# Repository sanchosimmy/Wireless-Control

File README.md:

/**
@mainpage Wireless home appliances control.

@author Akshay Pampatwar (Software)
@author Sancho Simmy Louis (Hardware Circuit Design)
@author Nijil George (Android App)
@author Sabitha Susan Joseph (PCB Design)

Appliances can be controlled via switches on a control board or a bluetooth mobile app. This project is developed for Tiva C tm4c123gh6pm uC. It can control following appliances:

(i)Fan

(ii)12 V Led strip

(iii)Plug1

(iv)Plug2

Hardware profiling of fan is done in the code thus even in case of low or over voltage of AC main line, Fan speed will remain constant for a given setting.
User specific setting of fan speed,led light brightness can be enabled from bluetooth app. 

In the starting, stored i.e. last values of Fan speed and Led Intensity will be used for control. 
Remainig inputs will be taken from hardware control panel i.e. switch board.
Thus in case of electricity failure, Fan speed and Led light brighteness will be restored but on/off state of appliances will depend on states of switches. User will have to resend commands via app for wireless control.

In case of multiple users, Latest command will be considered. 
Once commands are sent over a bluetooth, o/p states will remain unnchanged even if wireless link is lost. i.e. Switch status will be ignored, But changes in switch will be incorporarted. 
E.g. Currently switch for fan is on and fan is on. Now if turn off command sent wirelessly then fan will turned off. But if switch for fan is toggled from on to off and off to on then fan will be turned on (Even if wireless link exists thus latest command is considered for final state of o/p).

	Software is divided into 3 layers.

(i)Application layer

(ii)Middle layer

(iii)Hardware Abstraction layer

For time being, for simplicity many HAL functions are defined in a Middle layer files/module. e.g. Bluetooth,fan,led,plug etc.

	Working of code: 

(i) First code initializes all the o/p pins and i/p pins. Initiallly all the o/ps are off.

(ii)Status of fan speed and led light intensity is restored from eeprom.

(iii)Depending on status of switches appliances will be turned on.

(iv)If data is sent over a bluetooth then it will be decoded and stored in a global variable.

(v)Controller continuously checks changes in states of appliances (From Switchs or Wi Command) Depending on new commands will be enforced for turning on/off or change of speed of appliances.

(vi)New commands of fan speed and intensity will be saved in an eeprom.

	Read files from Documentation\html folder for more info on software / code.
*/

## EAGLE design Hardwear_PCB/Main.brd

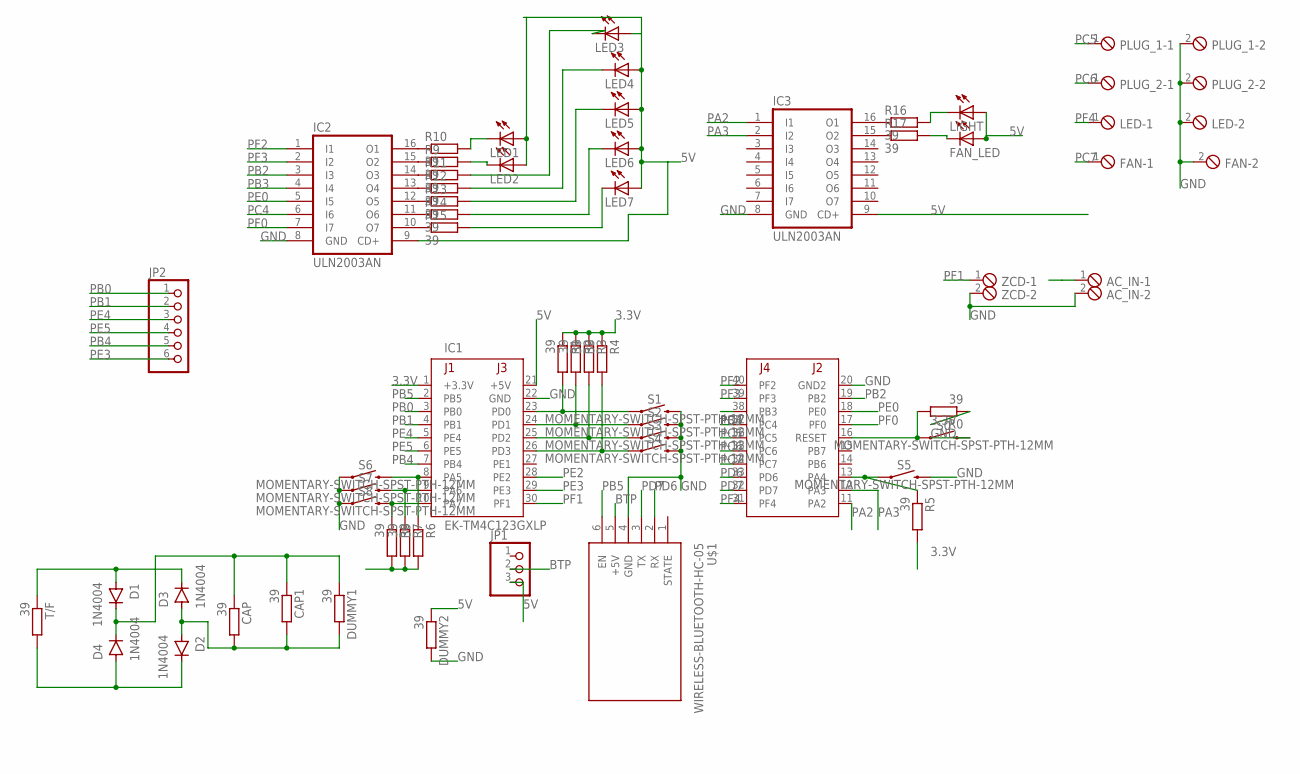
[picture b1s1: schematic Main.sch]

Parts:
AC_IN: MPT2; 2POL254
CAP, CAP1: 39; 0204/7
D1, D2, D3, D4: 1N4004; DO-41
DUMMY1, DUMMY2: 39; 0204/7
FAN: MPT2; 2POL254
FAN_LED: LED3MM
IC1: EK-TM4C123GXLP; TM4C123LAUNCHPAD
IC2, IC3: ULN2003AN; DIL16
JP1: PINHD-1X3CB; 1X03-CLEANBIG
JP2: PINHD-1X6; 1X06
LED: MPT2; 2POL254
LED1, LED2, LED3, LED4, LED5, LED6, LED7: LED3MM
LIGHT: LED3MM
PLUG_1, PLUG_2: MPT2; 2POL254
R0, R1, R2, R3, R4, R5, R6, R7, R8, R9, R10, R11, R12, R13, R14, R15, R16, R17: 39; 0204/7
S0, S1, S2, S3, S4, S5, S6, S7, S8: MOMENTARY-SWITCH-SPST-PTH-12MM; TACTILE_SWITCH_PTH_12MM
T/F: 39; 0204/7
U$1: WIRELESS-BLUETOOTH-HC-05
ZCD: MPT2; 2POL254

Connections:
3.3V: IC1.1 (+3.3V), R0.1, R1.1, R2.1, R3.1, R4.1, R5.2, R6.2, R7.2, R8.2
5V: DUMMY2.1, FAN_LED.A, IC1.21 (+5V), IC2.9 (CD+), IC3.9 (CD+), JP1.3, LED1.A, LED2.A, LED3.A, LED4.A, LED5.A, LED6.A, LED7.A, LIGHT.A
BTP: JP1.2, U$1.5 (+5V)
GND: AC_IN.2, DUMMY2.2, FAN.2, IC1.20 (GND2), IC1.22 (GND), IC2.8 (GND), IC3.8 (GND), LED.2, PLUG_1.2, PLUG_2.2, S0.3 (2), S1.3 (2), S2.3 (2), S3.3 (2), S4.3 (2), S5.3 (2), S6.1, S7.1, S8.1, U$1.4 (GND), ZCD.2
unnamed: IC1.23 (PD0), R1.2, S1.1
unnamed: IC1.24 (PD1), R2.2, S2.1
unnamed: IC1.25 (PD2), R3.2, S3.1
unnamed: IC1.26 (PD3), R4.2, S4.1
unnamed: IC1.13 (PA4), R5.1, S5.1
unnamed: IC1.8 (PA5), R6.1, S6.3 (2)
unnamed: IC1.16 (RESET), R0.2, S0.1
unnamed: IC1.9 (PA6), R7.1, S7.3 (2)
unnamed: IC1.10 (PA7), R8.1, S8.3 (2)
unnamed: IC2.15 (O2), R9.1
unnamed: IC2.16 (O1), R10.1
unnamed: IC2.14 (O3), R11.1
unnamed: IC2.13 (O4), R12.1
unnamed: D1.A, D3.C, T/F.1
unnamed: IC2.12 (O5), R13.1
unnamed: IC2.11 (O6), R14.1
unnamed: IC2.10 (O7), R15.1
unnamed: IC3.16 (O1), R16.1
unnamed: LED1.K (C), R10.2
unnamed: LED2.K (C), R9.2
unnamed: LED3.K (C), R11.2
unnamed: LED4.K (C), R12.2
unnamed: LED5.K (C), R13.2
unnamed: LED6.K (C), R14.2
unnamed: LED7.K (C), R15.2
unnamed: IC3.15 (O2), R17.1
unnamed: CAP.2, CAP1.2, D2.A, D3.A, DUMMY1.2
unnamed: CAP.1, CAP1.1, D1.C, D4.C, DUMMY1.1
unnamed: D2.C, D4.A, T/F.2
unnamed: LIGHT.K (C), R16.2
unnamed: FAN_LED.K (C), R17.2
PA2: IC1.11 (PA2), IC3.1 (I1)
PA3: IC1.12 (PA3), IC3.2 (I2)
PB0: IC1.3 (PB0), JP2.1
PB1: IC1.4 (PB1), JP2.2
PB2: IC1.19 (PB2), IC2.3 (I3)
PB3: IC1.38 (PB3), IC2.4 (I4)
PB4: IC1.7 (PB4), JP2.5
PB5: IC1.2 (PB5), U$1.6 (EN)
PC4: IC1.37 (PC4), IC2.6 (I6)
PC5: IC1.36 (PC5), PLUG_1.1
PC6: IC1.35 (PC6), PLUG_2.1
PC7: FAN.1, IC1.34 (PC7)
PD6: IC1.33 (PD6), U$1.2 (RX)
PD7: IC1.32 (PD7), U$1.3 (TX)
PE0: IC1.18 (PE0), IC2.5 (I5)
PE2: AC_IN.1, IC1.28 (PE2)
PE3: IC1.29 (PE3), JP2.6
PE4: IC1.5 (PE4), JP2.3
PE5: IC1.6 (PE5), JP2.4
PF0: IC1.17 (PF0), IC2.7 (I7)
PF1: IC1.30 (PF1), ZCD.1
PF2: IC1.40 (PF2), IC2.1 (I1)
PF3: IC1.39 (PF3), IC2.2 (I2)
PF4: IC1.31 (PF4), LED.1

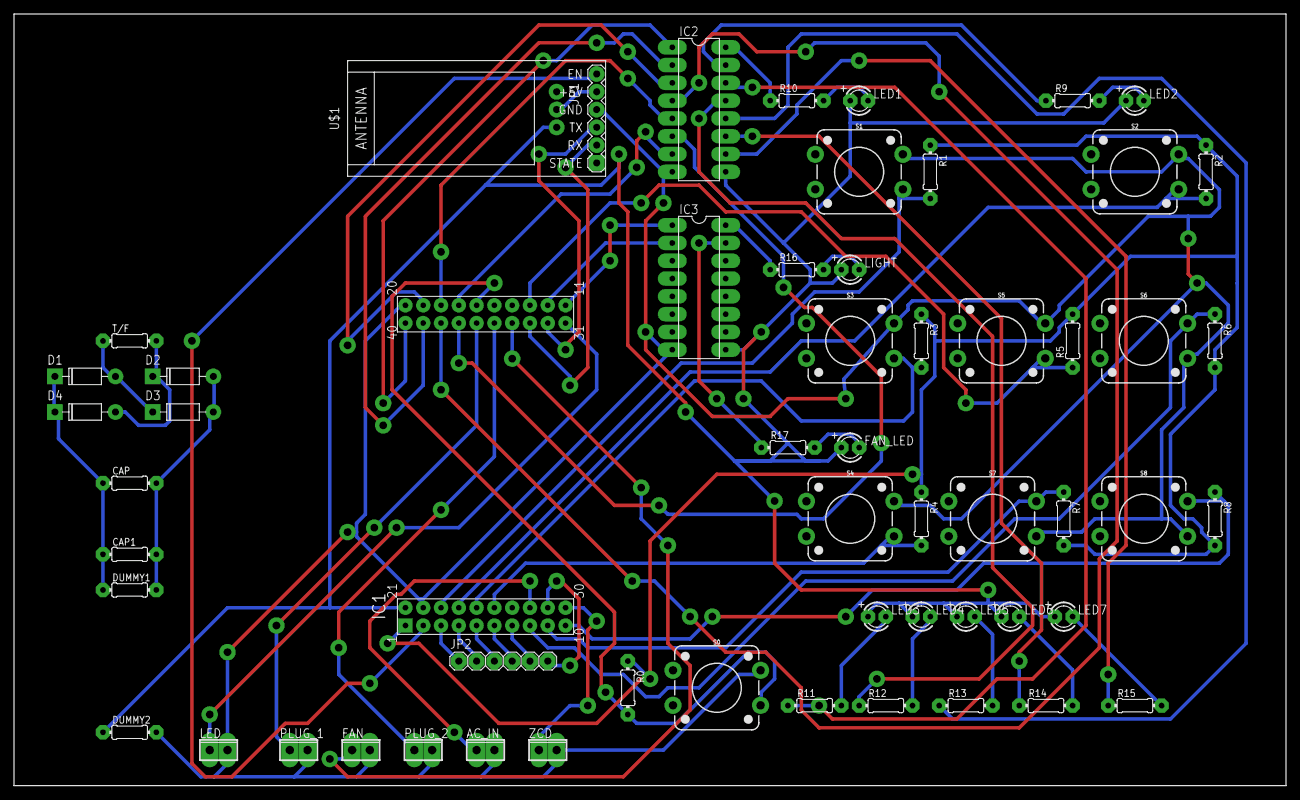
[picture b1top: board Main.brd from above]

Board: 2 copper layers, 181.6 x 110.2 mm, 57 parts (0 on the bottom side), 59 nets.

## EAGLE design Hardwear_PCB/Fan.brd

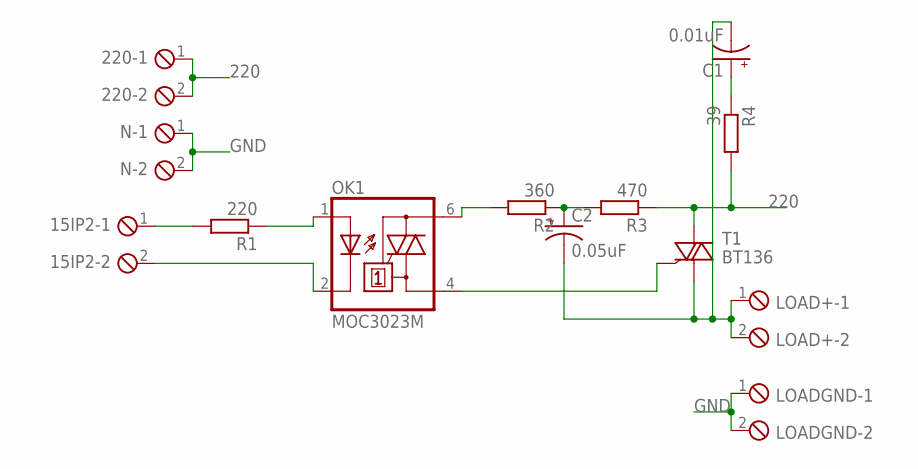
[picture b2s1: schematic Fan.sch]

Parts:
15IP2, 220: MPT2; 2POL254
C1: 0.01uF; CPOL-RADIAL-5MM-10MM
C2: 0.05uF; CPOL-RADIAL-5MM-10MM
LOAD+: MPT2; 2POL254
LOADGND: MPT2; 2POL254
N: MPT2; 2POL254
OK1: MOC3023M; DIL06
R1: 220; 0204/7
R2: 360; 0204/7
R3: 470; 0204/7
R4: 39; 0204/7
T1: BT136; TO220AB

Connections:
220: 220.1, 220.2, R3.1, R4.2, T1.2 (A2)
GND: LOADGND.1, LOADGND.2, N.1, N.2
unnamed: 15IP2.1, R1.2
unnamed: 15IP2.2, OK1.2 (C)
unnamed: OK1.1 (A), R1.1
unnamed: OK1.6 (A2), R2.2
unnamed: C2.+, R2.1, R3.2
unnamed: OK1.4 (A1), T1.3 (G)
unnamed: C1.+, R4.1
unnamed: C1.-, C2.-, LOAD+.1, LOAD+.2, T1.1 (A1)

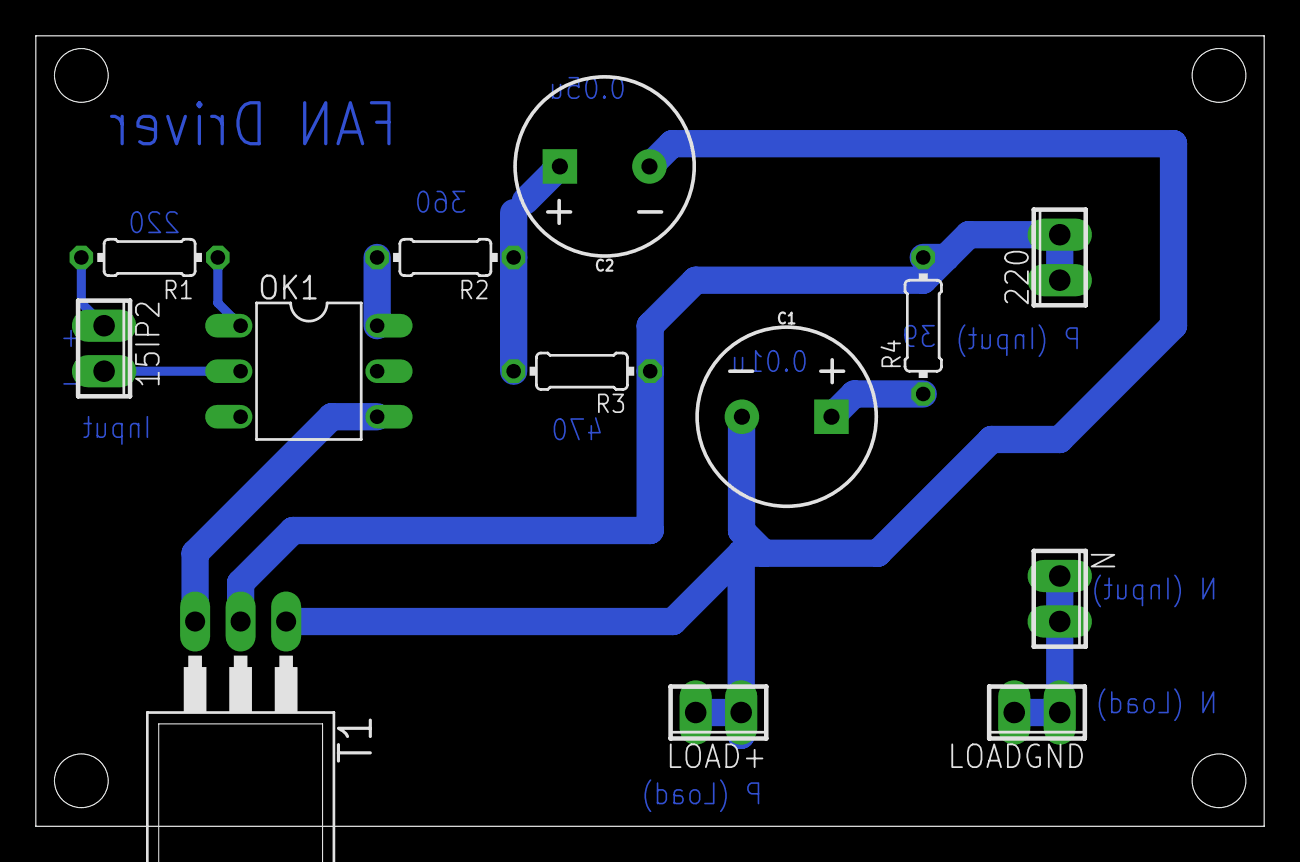
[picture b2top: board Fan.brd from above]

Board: 2 copper layers, 68.6 x 44.1 mm, 13 parts (0 on the bottom side), 10 nets.

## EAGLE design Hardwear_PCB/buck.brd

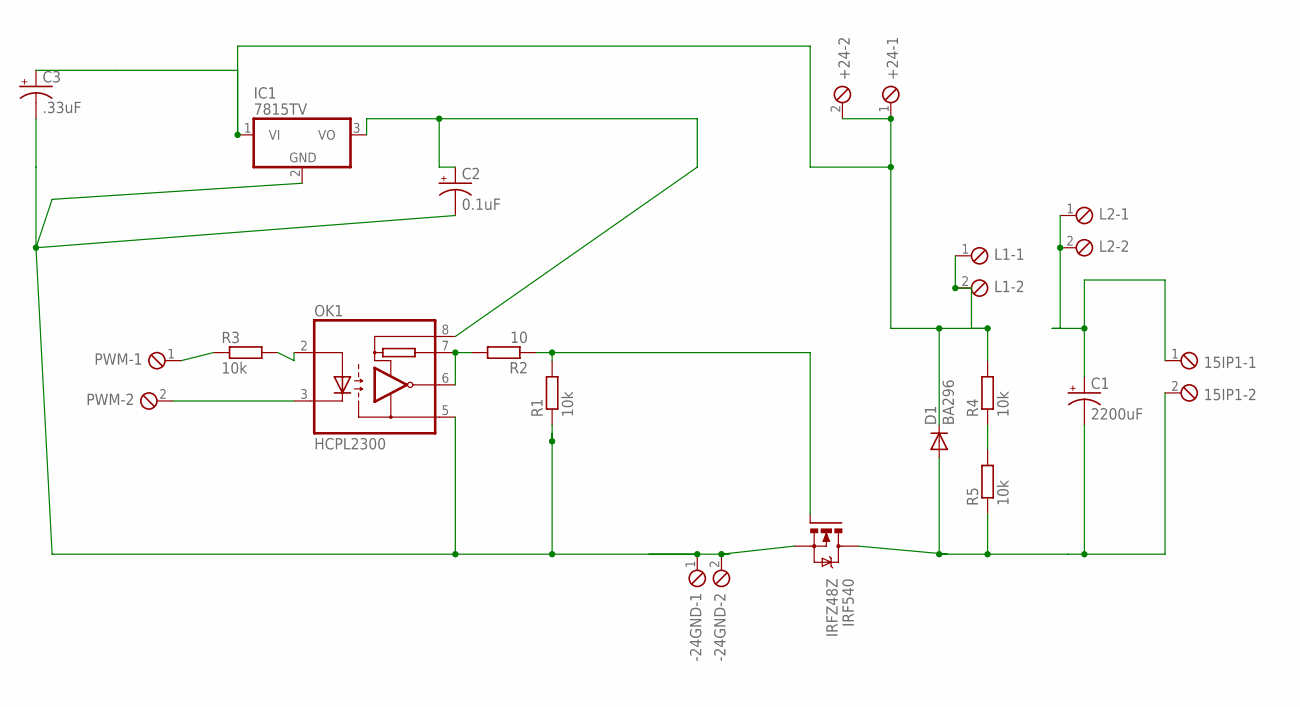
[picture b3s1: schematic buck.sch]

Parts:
15IP1: MPT2; 2POL254
+24: MPT2; 2POL254
-24GND: MPT2; 2POL254
C1: 2200uF; CPOL-RADIAL-5MM-10MM
C2: 0.1uF; CPOL-RADIAL-5MM-10MM
C3: .33uF; CPOL-RADIAL-5MM-10MM
D1: BA296; P2-15
IC1: 7815TV; TO220V
IRF540: IRFZ48Z; TO220BH
L1, L2: MPT2; 2POL254
OK1: HCPL2300; DIL08
PWM: MPT2; 2POL254
R1, R3, R4, R5: 10k; 0204/7
R2: 10; 0204/7

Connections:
GND: -24GND.1, -24GND.2, C2.-, C3.-, IC1.2 (GND), IRF540.S, OK1.5 (GND), R1.1
unnamed: PWM.1, R3.1
unnamed: R4.1, R5.2
unnamed: OK1.3 (C), PWM.2
unnamed: OK1.2 (A), R3.2
unnamed: +24.1, +24.2, C3.+, D1.C, IC1.1 (VI), L1.1, L1.2, R4.2
unnamed: 15IP1.2, C1.-, D1.A, IRF540.D, R5.1
unnamed: IRF540.G, R1.2, R2.1
unnamed: 15IP1.1, C1.+, L2.1, L2.2
unnamed: C2.+, IC1.3 (VO), OK1.8 (VCC)
unnamed: OK1.6 (VO), OK1.7 (RL), R2.2

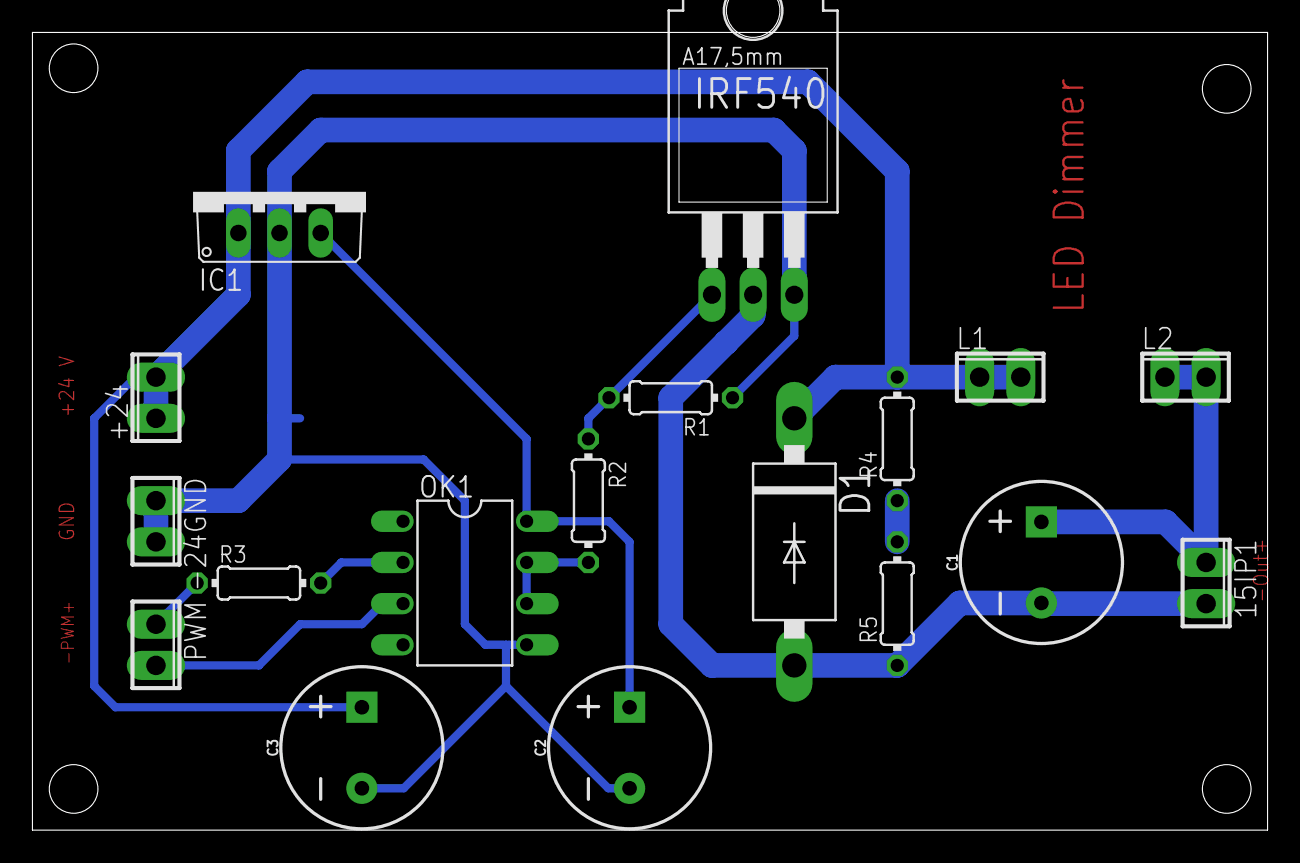
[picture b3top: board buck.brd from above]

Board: 2 copper layers, 76.2 x 49.2 mm, 18 parts (0 on the bottom side), 11 nets.

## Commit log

2020-04-22 Create LICENSE
2020-04-22 Readme file also for a software documentation
2020-04-22 Added location for more docs
2020-04-22 All pgm files coded in a corona lockdown period. Bluetooh.c and fn AcVtgRms(uint32_t) from fan.c are not complete. Project is not yet tested on hardware
2020-04-22 To check pull request in local repo
2020-04-22 To learn git hub
    ignore
2020-04-22 Changes in local repo
2020-04-22 Final version of code done in vacation
2020-08-02 Update README.md
    Added Role of each author in a project

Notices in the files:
parts and their libraries:
SparkFun-Capacitors: Licensing: Creative Commons ShareAlike 4.0 International - https://creativecommons.org/licenses/by-sa/4.0
diy-modules: Released under the Creative Commons Attribution 4.0 International License: http://creativecommons.org/licenses/by/4.0
